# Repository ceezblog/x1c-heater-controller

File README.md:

# This is just a fun project to spend some free time. I haven't tested it yet. 
- The code included is a very simple code to control temperature of the heater of x1c hotend for cleaning the hotend which I haven't run yet. I don't have x1c to test with.
- I assume, the NTC of hotend is 100k ohm, please check if the correct connectors for heater/thermistor are used.
- Run this with 12V-2A DC instead of 24V. Arduino nano cannot run from 24v power adaptor. It will get hot slower but it is safer as well.

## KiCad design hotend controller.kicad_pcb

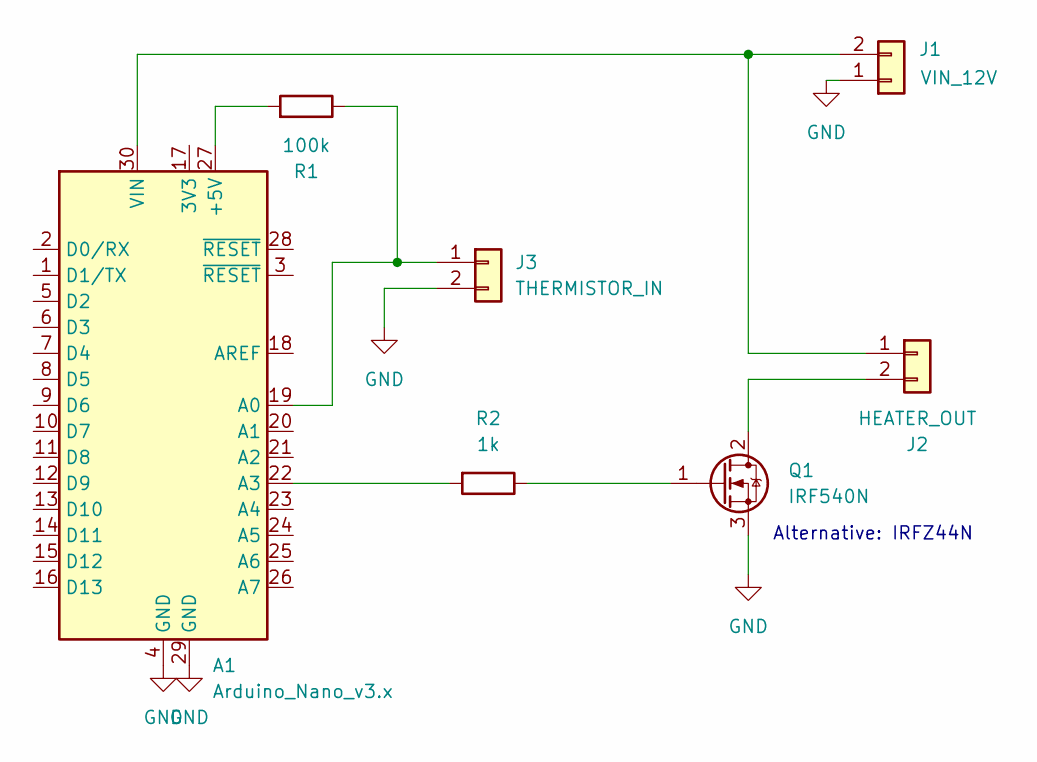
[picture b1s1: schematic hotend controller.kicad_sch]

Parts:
A1: Arduino_Nano_v3.x; Arduino_Nano
J1: VIN_12V; TerminalBlock_bornier-2_P5.08mm
J2: HEATER_OUT; JST_XH_B2B-XH-A_1x02_P2.50mm_Vertical
J3: THERMISTOR_IN; JST_PH_B2B-PH-K_1x02_P2.00mm_Vertical
Q1: IRF540N; TO-220-3_Vertical
R1: 100k; R_Axial_DIN0207_L6.3mm_D2.5mm_P10.16mm_Horizontal
R2: 1k; R_Axial_DIN0207_L6.3mm_D2.5mm_P10.16mm_Horizontal

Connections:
GND: A1.4 (GND), A1.29 (GND), J1.1, J3.2, Q1.3 (S)
unnamed: A1.27 (+5V), R1.2
unnamed: A1.19 (A0), J3.1, R1.1
unnamed: A1.22 (A3), R2.2
unnamed: A1.30 (VIN), J1.2, J2.1
unnamed: J2.2, Q1.2 (D)
unnamed: Q1.1 (G), R2.1

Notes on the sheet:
Alternative: IRFZ44N

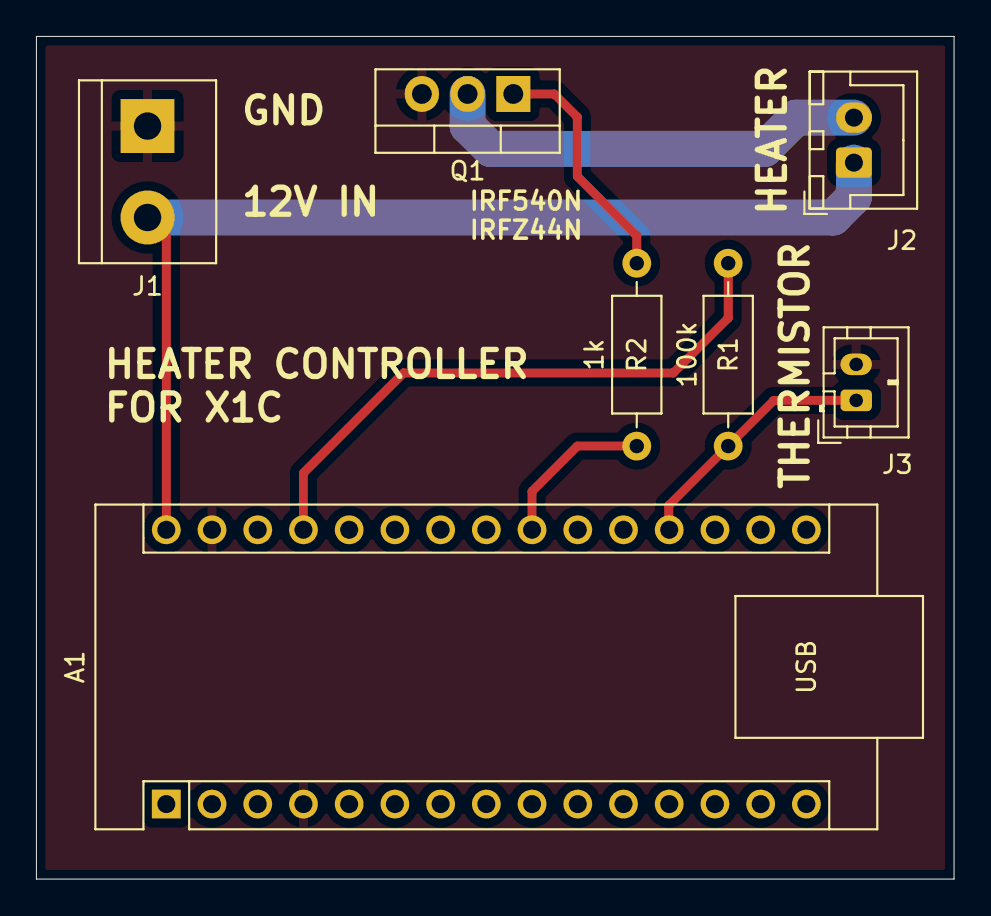
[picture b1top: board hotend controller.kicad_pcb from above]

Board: 2 copper layers, 51.0 x 46.8 mm, 7 parts (0 on the bottom side), 7 nets.
